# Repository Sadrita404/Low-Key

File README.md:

<div align="center">
  <table border="0" cellpadding="0" cellspacing="0">
    <tr>
      <td align="center" style="background: #ffffff; border: 1px solid #d0d7de; border-radius: 12px; padding: 16px; box-shadow: 0 4px 12px rgba(0,0,0,0.05);">
        
        <div style="margin-top: 12px; font-family: -apple-system, BlinkMacSystemFont, 'Segoe UI', Helvetica, Arial, sans-serif; font-size: 13px; color: #57606a; font-weight: 500;">
      </td>
    </tr>
  </table>
</div>

|Title | Low Key |
|:-- |:--|
|Author | Sadrita Neogi|

## Overview
It is a 60% Low Profile Keyboard trying to build an mac magic keyboard alternative. And for this project I have choose the Promicro NRF52840 Controller Board as it is cost effective and easy to setup . I have also make this keyboard too low profile so that it can be easy to type in it . I have also make it battery powered and It can be worked over bluetooth that makes it very easy to use.

### Why I choose this project?
I have choose this project because I have a big fan of the Apple magic keyboard due to its low profile and good looking so from the starting I wanted to create something like which is low profile. But if I going to buy one, it would cost me a lot and I cannot customise it so I wanted to make something which is customisable, so I have made this in the 60% layout keyboard which is in the low profile and I love to make it and I have also made the PCB so I can customise it. I have also put my name on the PCB. And I have loved the whole process from designing in the PCB to making assembly file in fusion

<div id="-screenshots" align="center">
  <h3>PCB Design</h3>

  <table>
    <tr>
      <td>
        
      </td>
      <td>
        
      </td>
    </tr>
    <tr>
      <td>
        
      </td>
      <td>
        
      </td>
    </tr>
  </table>
</div>

<div id="-screenshots" align="center">
  <h3>PCB </h3>

  <table>
    <tr>
      <td>
        
      </td>
      <td>
        
      </td>
    </tr>
    <tr>
      <td>
        
      </td>
      <td>
        
      </td>
    </tr>
  </table>
</div>

<div id="-screenshots" align="center">
  <h3>CAD Work </h3>

  <table>
    <tr>
      <td>
        
      </td>
      <td>
        
      </td>
    </tr>
    <tr>
      <td>
        
      </td>
      <td>
        
      </td>
    </tr>
  </table>
</div>

<div id="-screenshots" align="center">
  <h3> Assembly CAD Work </h3>
  <table>
    <tr>
      <td>
        
      </td>
      <td>
        
      </td>
    </tr>
    <tr>
      <td>
        
      </td>
      <td>
        
      </td>
    </tr>
  </table>
</div>

<!-- FRONT & BACK VIEW SHOWCASE -->
<div align="center">
  <h2> Final Look After Assembly </h2>
</div>

---

<!-- TWO-COLUMN IMAGE FRAME GRID -->
<div align="center">
  <table border="0" cellpadding="10" cellspacing="0" style="border-collapse: collapse;">
    <tr>
      <!-- FRONT SIDE CARD -->
      <td align="center" valign="top" width="50%" style="background: #ffffff; border: 1px solid #d0d7de; border-radius: 12px; padding: 16px; box-shadow: 0 4px 12px rgba(0,0,0,0.05);">
        
        <div style="margin-top: 12px; font-family: -apple-system, BlinkMacSystemFont, 'Segoe UI', Helvetica, Arial, sans-serif; font-size: 13px; color: #57606a; font-weight: 600; text-transform: uppercase; letter-spacing: 0.5px;">
        </div>
      </td>
      <!-- SPACER FOR GITHUB MOBILE DEGRADATION -->
      <td width="2%">&nbsp;</td>
      <!-- BACK SIDE CARD -->
      <td align="center" valign="top" width="50%" style="background: #ffffff; border: 1px solid #d0d7de; border-radius: 12px; padding: 16px; box-shadow: 0 4px 12px rgba(0,0,0,0.05);">
        
        <div style="margin-top: 12px; font-family: -apple-system, BlinkMacSystemFont, 'Segoe UI', Helvetica, Arial, sans-serif; font-size: 13px; color: #57606a; font-weight: 600; text-transform: uppercase; letter-spacing: 0.5px;">
        </div>
      </td>
    </tr>
  </table>
</div>

<!-- TWO-COLUMN IMAGE FRAME GRID -->
<div align="center">
  <table border="0" cellpadding="10" cellspacing="0" style="border-collapse: collapse;">
    <tr>
      <!-- FRONT SIDE CARD -->
      <td align="center" valign="top" width="50%" style="background: #ffffff; border: 1px solid #d0d7de; border-radius: 12px; padding: 16px; box-shadow: 0 4px 12px rgba(0,0,0,0.05);">
        
        <div style="margin-top: 12px; font-family: -apple-system, BlinkMacSystemFont, 'Segoe UI', Helvetica, Arial, sans-serif; font-size: 13px; color: #57606a; font-weight: 600; text-transform: uppercase; letter-spacing: 0.5px;">
        </div>
      </td>
      <!-- SPACER FOR GITHUB MOBILE DEGRADATION -->
      <td width="2%">&nbsp;</td>
      <!-- BACK SIDE CARD -->
      <td align="center" valign="top" width="50%" style="background: #ffffff; border: 1px solid #d0d7de; border-radius: 12px; padding: 16px; box-shadow: 0 4px 12px rgba(0,0,0,0.05);">
        
        <div style="margin-top: 12px; font-family: -apple-system, BlinkMacSystemFont, 'Segoe UI', Helvetica, Arial, sans-serif; font-size: 13px; color: #57606a; font-weight: 600; text-transform: uppercase; letter-spacing: 0.5px;">
        </div>
      </td>
    </tr>
  </table>
</div>

<div align="center">
  <h2> Bill of Materials</h2>
</div>

| Component Name | Purpose | Qty | Unit Price | Total Price | Source Link |
| :--- | :--- | :---: | :---: | :---: | :---: |
| **3.7V 1000mAh Lipo Battery** | For Power | 1 | $4.00 | $4.00 | [Robu](https://robu.in/product/wly394058-1000mah-3-7v-single-cell-rechargeable-lipo-battery/) |
| **1N4148W - Diodes** | For PCB | 64 | $0.02 | $1.22 | [Robu](https://robu.in/product/1n4148w-slkor-75v-1v-4ns-150ma-sod-123-switching-diodes-rohs/) |
| **Header Pin** | For PCB | 2 | $0.58 | $1.16 | [Lion Circuits](https://www.lioncircuits.com/parts/M20-8770542) |
| **Switch Slide SPDT** | For Power On and OFF | 1 | $1.70 | $1.70 | [Lion Circuits](https://www.lioncircuits.com/parts/SSSS811101) |
| **Screw(M4x10mm)** | For Fixing | 4 | $0.023 | $0.093 | [Onlyscrew](https://onlyscrews.in/products/m4-x-10mm-hex-allen-button-head-high-tensile10-9-black-oxide-screw-dia-4mm-length-10mm?currency=INR&country=IN&variant=49998575993145&stkn=6e84ebfba1b8&utm_source=google&utm_medium=cpc&utm_campaign=inderans_campaign_copy&gad_source=1&gad_campaignid=22930701107&gbraid=0AAAAA9sP2SSC2iobyr1JnmoScJm2hhdWI&gclid=CjwKCAjw6f3RBhApEiwAMaCqWeeqy7ts2FHdbF68ClVPVea7u91EIUDmBj3ym2QF8aJOrLDm1FMqjBoCckkQAvD_BwE) |
| **Hot-swap Socket** | For the PCB | 64 | $0.10 | $6.15 | [Meckeys](https://meckeys.com/shop/accessories/keyboard-accessories/key-switches/kailh-hot-swap-socket/) |
| **Plate Mount Stabilizers** | For the Keys | 2 | $2.10 | $4.20 | [GenesisPC](https://www.genesispc.in/products/durock-plate-mount-stabilizers-6-25u-4x2u-black) |
| **Promicro NRF52840** | Main Controller Board | 1 | $8.05 | $8.05 | [Robu](https://robu.in/product/promicro-nrf52840-development-board/) |
| **Keycaps** | For adding on the switches | 64 | $0.33 | $21.20 | [CtrlShiftStore](https://ctrlshiftstore.com/products/xvx-skyline-r2) |
| **3 pin Low Profile Switch** | For the PCB board | 64 | $0.20 | $12.70 | [Meckeys](https://meckeys.com/shop/accessories/keyboard-accessories/key-switches/gateron-low-profile-2-0-mechanical-switch-3pin/) |
| **PCB** | Main Board | 1 | $16.00 | $16.00 | [JLCPCB](https://jlcpcb.com/) |
| **Total Project Cost** | | | | **$76.38** | |

<div align="center">
  <table border="0" cellpadding="0" cellspacing="0" style="border-collapse: collapse; max-width: 600px;">
    <tr>
      <td style="background: #ffffff; border: 1px solid #d0d7de; border-radius: 12px; padding: 20px; box-shadow: 0 4px 12px rgba(0,0,0,0.05); font-family: -apple-system, BlinkMacSystemFont, 'Segoe UI', Helvetica, Arial, sans-serif;">
        <div style="font-size: 16px; font-weight: 600; color: #24292f; margin-bottom: 12px; border-bottom: 1px solid #d0d7de; padding-bottom: 8px;">
          Final Bill
        </div>
        <table width="100%" border="0" style="border-collapse: collapse; font-size: 14px; color: #57606a;">
          <tr>
            <td style="padding: 4px 0;">Component Subtotal:</td>
            <td align="right" style="font-weight: 500; color: #24292f;">$76.38</td>
          </tr>
          <tr>
            <td style="padding: 4px 0;"> Shipping:</td>
            <td align="right" style="font-weight: 500; color: #24292f;">$21.19</td>
          </tr>
          <tr>
            <td style="padding: 4px 0; padding-bottom: 8px;"> Tax:</td>
            <td align="right" style="font-weight: 500; color: #24292f;">$2</td>
          </tr>
          <tr style="border-top: 1px dashed #d0d7de;">
            <td style="padding: 12px 0 0 0; font-weight: 600; color: #24292f; font-size: 15px;">Net Total Cost:</td>
            <td align="right" style="padding: 12px 0 0 0; font-weight: bold; color: #2da44e; font-size: 18px;">$99.57</td>
          </tr>
          <tr>
            <td style="padding: 2px 0 0 0; font-size: 11px; color: #8c959f;">Projected Budget Allocation:</td>
            <td align="right" style="padding: 2px 0 0 0; font-weight: 500; font-size: 12px; color: #8c959f;">$100</td>
          </tr>
        </table>
      </td>
    </tr>
  </table>
</div>

I have provided the links to the parts that I will self - sourced , So that if a reader wanted to recreate this project they would be able to find all the parts..
Which is also updated on the BOM csv file too..

**Project Under Hack Club**

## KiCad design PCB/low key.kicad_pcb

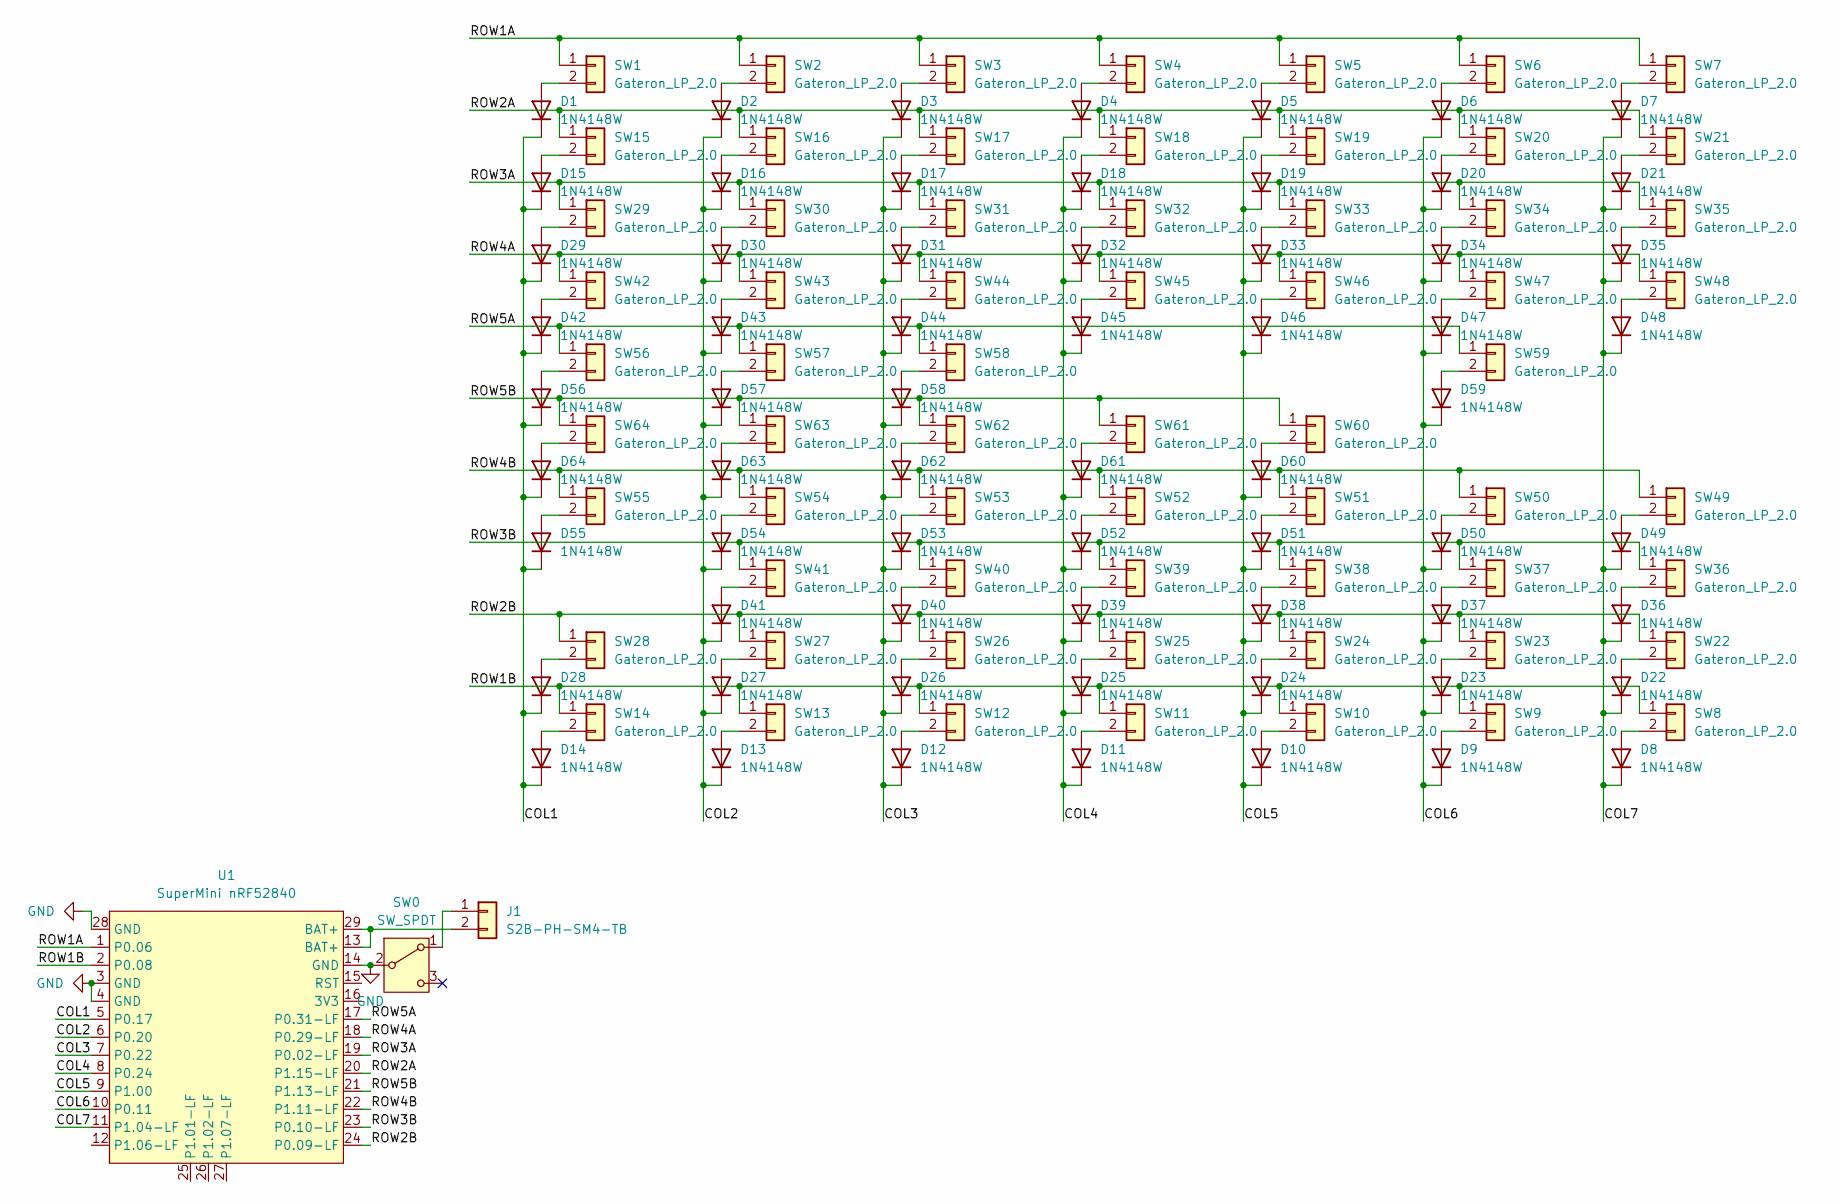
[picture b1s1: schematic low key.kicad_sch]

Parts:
D1, D2, D3, D4, D5, D6, D7, D8, D9, D10, D11, D12, D13, D14, D15, D16, D17, D18, D19, D20, D21, D22, D23, D24, D25, D26, D27, D28, D29, D30, D31, D32, D33, D34, D35, D36, D37, D38, D39, D40, D41, D42, D43, D44, D45, D46, D47, D48, D49, D50, D51, D52, D53, D54, D55, D56, D57, D58, D59, D60, D61, D62, D63, D64: 1N4148W; D_SOD-123
J1: S2B-PH-SM4-TB; JST_PH_S2B-PH-SM4-TB_1x02-1MP_P2.00mm_Horizontal
SW0: SW_SPDT; SW_SSSS811101
SW1, SW2, SW3, SW4, SW5, SW6, SW7, SW8, SW9, SW10, SW11, SW12, SW13, SW14, SW15, SW16, SW17, SW18, SW19, SW20, SW21, SW22, SW23, SW24, SW25, SW26, SW27, SW28, SW29, SW30, SW31, SW32, SW33, SW34, SW35, SW36, SW37, SW38, SW39, SW40, SW41, SW42, SW43, SW44, SW45, SW46, SW47, SW48, SW49, SW50, SW51, SW52, SW53, SW54, SW55, SW56, SW57, SW58, SW59, SW60, SW61, SW62, SW63, SW64: Gateron_LP_2.0
U1: SuperMini nRF52840; SuperMini_nRF52840_AH_USBup

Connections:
/COL1: D1.1 (K), D14.1 (K), D15.1 (K), D28.1 (K), D29.1 (K), D42.1 (K), D55.1 (K), D56.1 (K), D64.1 (K), U1.5 (P0.17)
/COL2: D2.1 (K), D13.1 (K), D16.1 (K), D27.1 (K), D30.1 (K), D41.1 (K), D43.1 (K), D54.1 (K), D57.1 (K), D63.1 (K), U1.6 (P0.20)
/COL3: D3.1 (K), D12.1 (K), D17.1 (K), D26.1 (K), D31.1 (K), D40.1 (K), D44.1 (K), D53.1 (K), D58.1 (K), D62.1 (K), U1.7 (P0.22)
/COL4: D4.1 (K), D11.1 (K), D18.1 (K), D25.1 (K), D32.1 (K), D39.1 (K), D45.1 (K), D52.1 (K), D61.1 (K), U1.8 (P0.24)
/COL5: D5.1 (K), D10.1 (K), D19.1 (K), D24.1 (K), D33.1 (K), D38.1 (K), D46.1 (K), D51.1 (K), D60.1 (K), U1.9 (P1.00)
/COL6: D6.1 (K), D9.1 (K), D20.1 (K), D23.1 (K), D34.1 (K), D37.1 (K), D47.1 (K), D50.1 (K), D59.1 (K), U1.10 (P0.11)
/COL7: D7.1 (K), D8.1 (K), D21.1 (K), D22.1 (K), D35.1 (K), D36.1 (K), D48.1 (K), D49.1 (K), U1.11 (P1.04-LF)
/ROW1A: SW1.1, SW2.1, SW3.1, SW4.1, SW5.1, SW6.1, SW7.1, U1.1 (P0.06)
/ROW1B: SW8.1, SW9.1, SW10.1, SW11.1, SW12.1, SW13.1, SW14.1, U1.2 (P0.08)
/ROW2A: SW15.1, SW16.1, SW17.1, SW18.1, SW19.1, SW20.1, SW21.1, U1.20 (P1.15-LF)
/ROW2B: SW22.1, SW23.1, SW24.1, SW25.1, SW26.1, SW27.1, SW28.1, U1.24 (P0.09-LF)
/ROW3A: SW29.1, SW30.1, SW31.1, SW32.1, SW33.1, SW34.1, SW35.1, U1.19 (P0.02-LF)
/ROW3B: SW36.1, SW37.1, SW38.1, SW39.1, SW40.1, SW41.1, U1.23 (P0.10-LF)
/ROW4A: SW42.1, SW43.1, SW44.1, SW45.1, SW46.1, SW47.1, SW48.1, U1.18 (P0.29-LF)
/ROW4B: SW49.1, SW50.1, SW51.1, SW52.1, SW53.1, SW54.1, SW55.1, U1.22 (P1.11-LF)
/ROW5A: SW56.1, SW57.1, SW58.1, SW59.1, U1.17 (P0.31-LF)
/ROW5B: SW60.1, SW61.1, SW62.1, SW63.1, SW64.1, U1.21 (P1.13-LF)
GND: SW0.2 (B), U1.3 (GND), U1.4 (GND), U1.14 (GND), U1.28 (GND)
unnamed: D1.2 (A), SW1.2
unnamed: D2.2 (A), SW2.2
unnamed: D3.2 (A), SW3.2
unnamed: D4.2 (A), SW4.2
unnamed: D5.2 (A), SW5.2
unnamed: D6.2 (A), SW6.2
unnamed: D7.2 (A), SW7.2
unnamed: D8.2 (A), SW8.2
unnamed: D9.2 (A), SW9.2
unnamed: D10.2 (A), SW10.2
unnamed: D11.2 (A), SW11.2
unnamed: D12.2 (A), SW12.2
unnamed: D13.2 (A), SW13.2
unnamed: D14.2 (A), SW14.2
unnamed: D15.2 (A), SW15.2
unnamed: D16.2 (A), SW16.2
unnamed: D17.2 (A), SW17.2
unnamed: D18.2 (A), SW18.2
unnamed: D19.2 (A), SW19.2
unnamed: D20.2 (A), SW20.2
unnamed: D21.2 (A), SW21.2
unnamed: D22.2 (A), SW22.2
unnamed: D23.2 (A), SW23.2
unnamed: D24.2 (A), SW24.2
unnamed: D25.2 (A), SW25.2
unnamed: D26.2 (A), SW26.2
unnamed: D27.2 (A), SW27.2
unnamed: D28.2 (A), SW28.2
unnamed: D29.2 (A), SW29.2
unnamed: D30.2 (A), SW30.2
unnamed: D31.2 (A), SW31.2
unnamed: D32.2 (A), SW32.2
unnamed: D33.2 (A), SW33.2
unnamed: D34.2 (A), SW34.2
unnamed: D35.2 (A), SW35.2
unnamed: D36.2 (A), SW36.2
unnamed: D37.2 (A), SW37.2
unnamed: D38.2 (A), SW38.2
unnamed: D39.2 (A), SW39.2
unnamed: D40.2 (A), SW40.2
unnamed: D41.2 (A), SW41.2
unnamed: D42.2 (A), SW42.2
unnamed: D43.2 (A), SW43.2
unnamed: D44.2 (A), SW44.2
unnamed: D45.2 (A), SW45.2
unnamed: D46.2 (A), SW46.2
unnamed: D47.2 (A), SW47.2
unnamed: D48.2 (A), SW48.2
unnamed: D49.2 (A), SW49.2
unnamed: D50.2 (A), SW50.2
unnamed: D51.2 (A), SW51.2
unnamed: D52.2 (A), SW52.2
unnamed: D53.2 (A), SW53.2
unnamed: D54.2 (A), SW54.2
unnamed: D55.2 (A), SW55.2
unnamed: D56.2 (A), SW56.2
unnamed: D57.2 (A), SW57.2
unnamed: D58.2 (A), SW58.2
unnamed: D59.2 (A), SW59.2
unnamed: D60.2 (A), SW60.2
unnamed: D61.2 (A), SW61.2
unnamed: D62.2 (A), SW62.2
unnamed: D63.2 (A), SW63.2
unnamed: D64.2 (A), SW64.2
unnamed: J1.1, SW0.1 (A)
unnamed: J1.2, U1.13 (BAT+), U1.29 (BAT+)

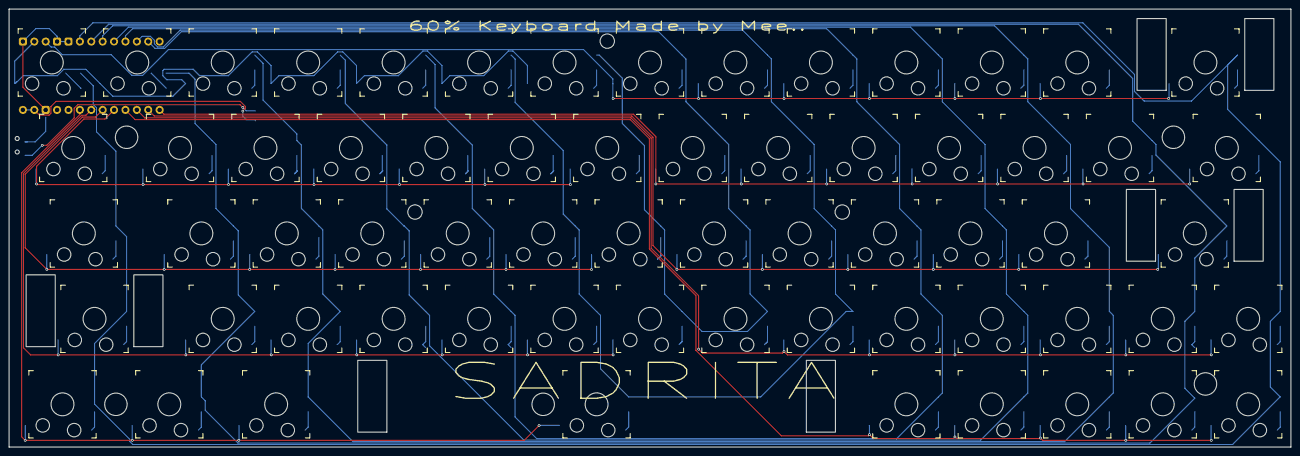
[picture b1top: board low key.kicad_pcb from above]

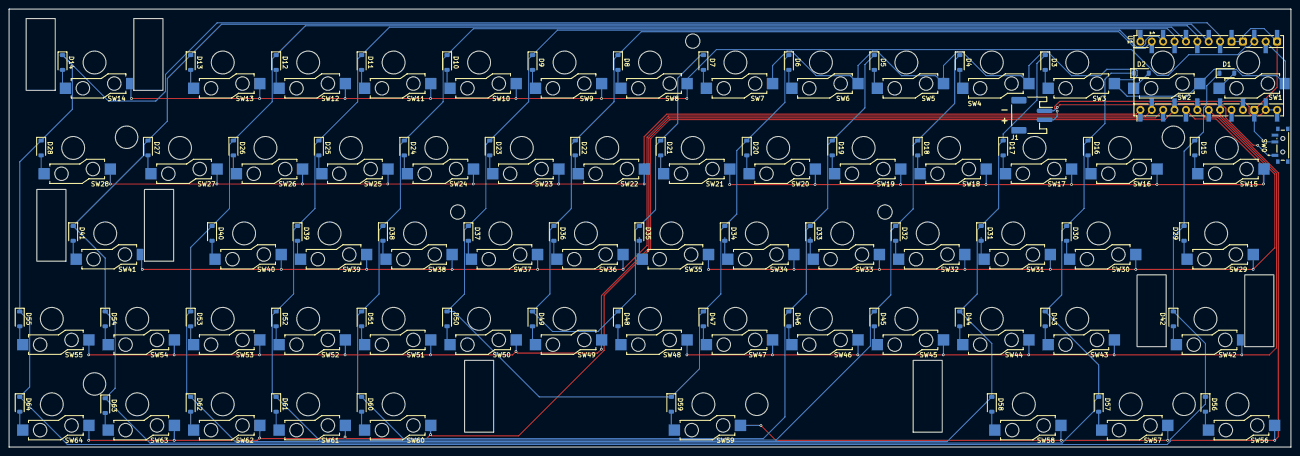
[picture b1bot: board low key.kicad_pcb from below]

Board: 2 copper layers, 285.7 x 97.6 mm, 131 parts (67 on the bottom side), 84 nets.

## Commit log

2026-06-18 bill screenshot added
2026-06-18 CAD all step file added
2026-06-18 PCB GERBER added
2026-06-18 all project image added
2026-06-18 all STL file for print added
2026-06-19 Gerber zip added
2026-06-25 Add project motivation to README
    Added a section explaining the motivation behind the project.
